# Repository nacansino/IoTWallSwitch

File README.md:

# IoTWallSwitch
An open-source IoT Wall Switch based on ESP device. I based this project on Xoseperez's [espurna-board project](https://github.com/xoseperez/espurna-board).

I aim this project to be a foundation of many small projects that ran on tap power supply.

## Block Diagram

## Primary Functionalities (User perspective):
1. Act as an on/off switch of an alternating or direct current load; the method of switching shall be done via physical access (e.g. button, capacitive touch) or via wirelessly (web interface, telnet, etc.)
2. Has the capability to measure the power consumed by the load, and to report it to an external entity (cloud, local household server).
3. Support more than one wireless protocol for redundancy
4. Has the capability to update functionality after deployment without physical access (over-the-air or OTA updates).

## Tech Stack
- Schematic and Layout: KiCAD
- Toolchain: TBA, currently thinking of building over ESP-IDF
- Unit Testing: CppUTest

## Applications:
- Generic Smart Switch for any load below 10A
- Household and industrial lighting
- Small motors/fans/pumps
- Desktop/Laptop Charger
- Television
- Speakers

## 3D Preview

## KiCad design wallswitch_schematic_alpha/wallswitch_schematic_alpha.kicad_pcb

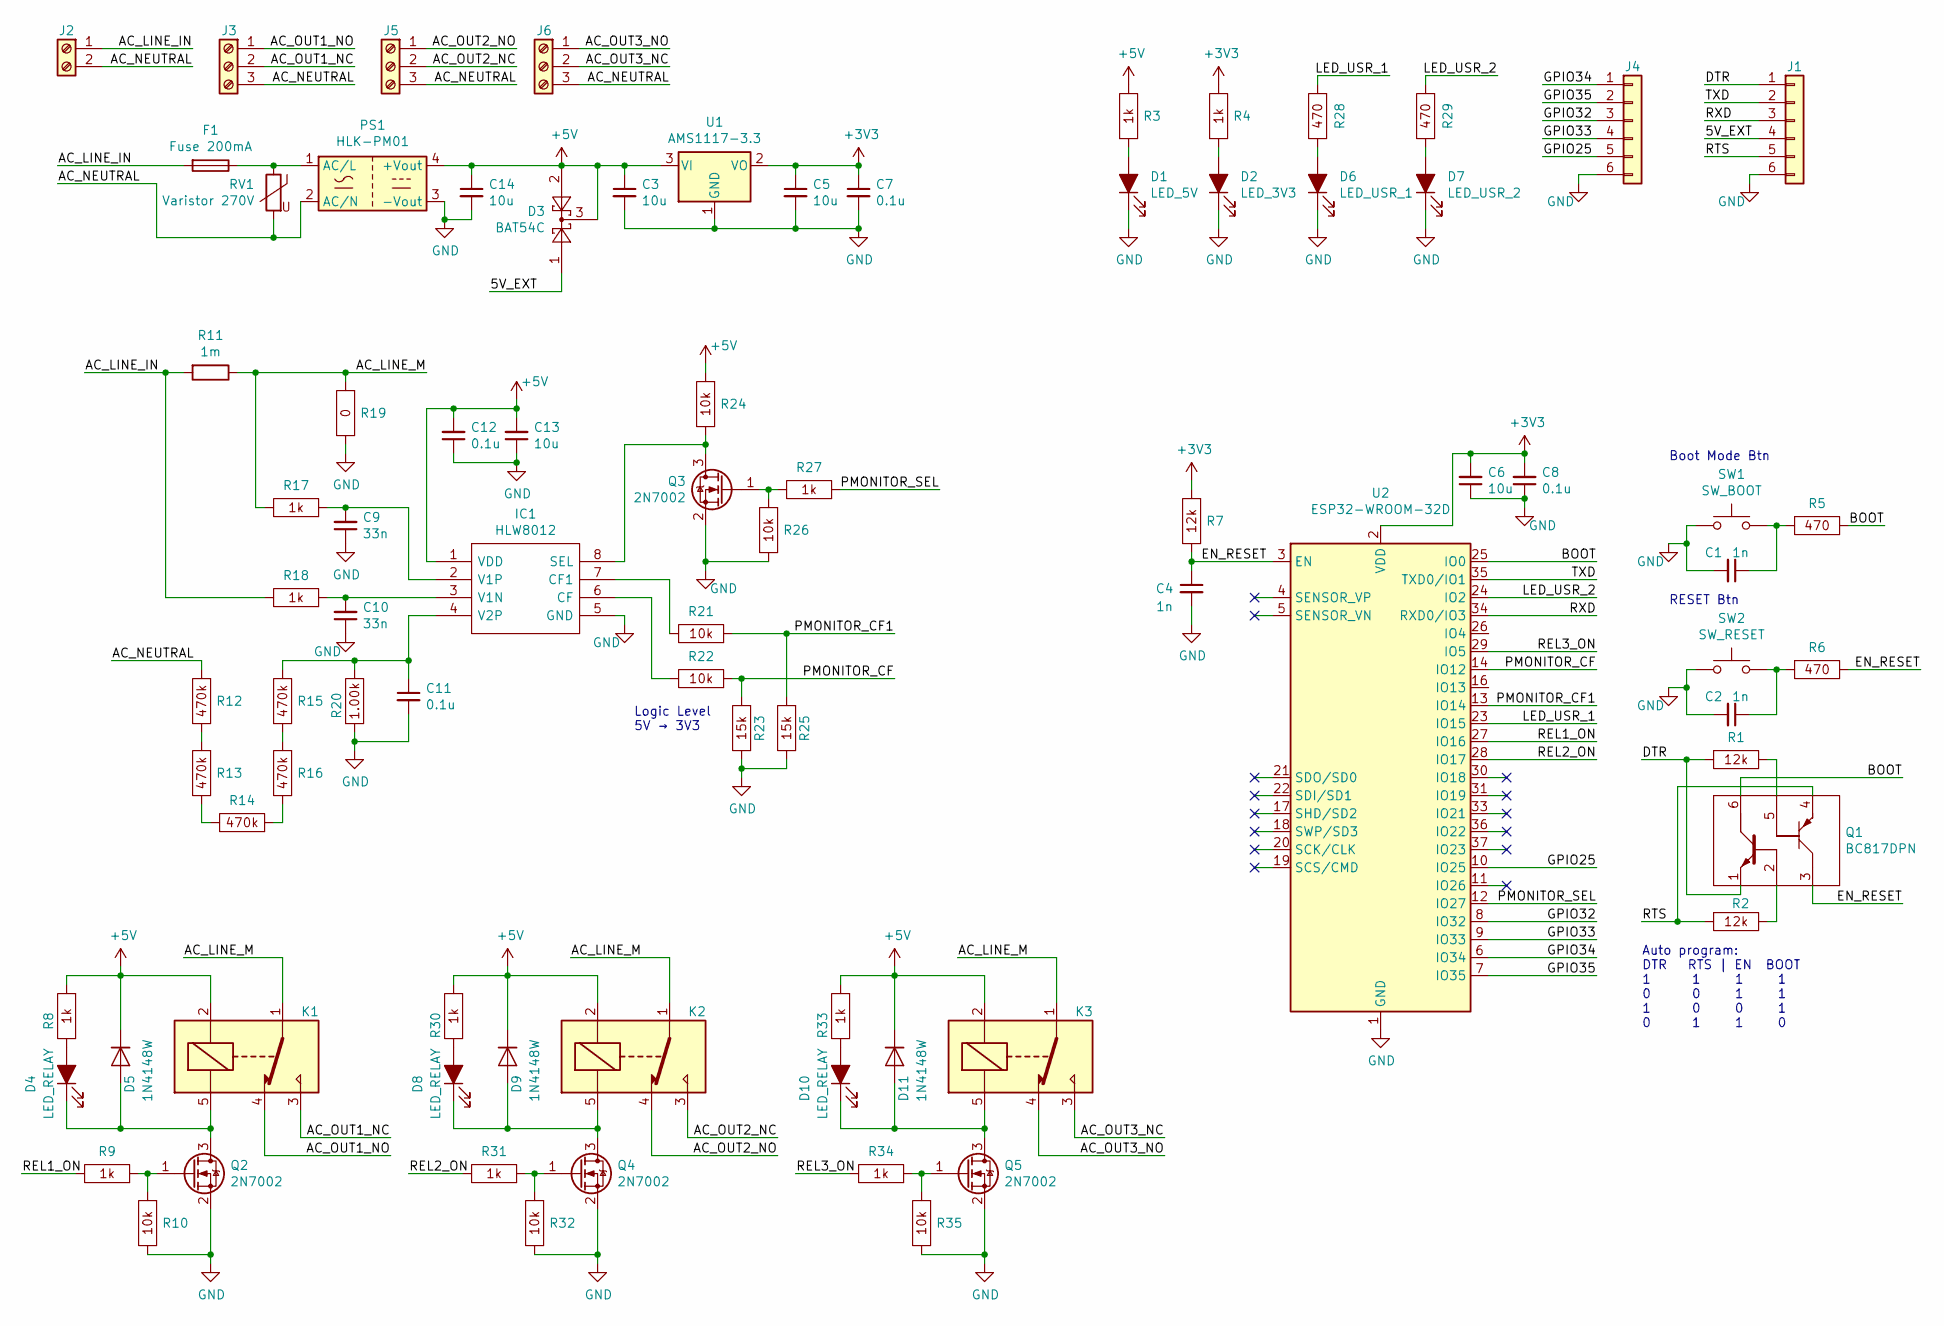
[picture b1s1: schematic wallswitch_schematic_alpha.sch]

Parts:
C1, C2, C4: 1n; C_0603_1608Metric
C3, C5, C6, C13, C14: 10u; C_0603_1608Metric
C7, C8, C11, C12: 0.1u; C_0603_1608Metric
C9, C10: 33n; C_0603_1608Metric
D1: LED_5V; LED_0603_1608Metric
D2: LED_3V3; LED_0603_1608Metric
D3: BAT54C; SOT-23
D4, D8, D10: LED_RELAY; LED_0603_1608Metric
D5, D9, D11: 1N4148W; D_SOD-123
D6: LED_USR_1; LED_0603_1608Metric
D7: LED_USR_2; LED_0603_1608Metric
F1: Fuse 200mA; Fuse_Blade_Mini_directSolder
IC1: HLW8012; SOIC127P600X170-8N; Manufacturer_Part_Number HLW8012
J1, J4: Conn_01x06; PinHeader_1x06_P2.54mm_Vertical
J2: Screw_Terminal_01x02; TerminalBlock_bornier-2_P5.08mm
J3, J5, J6: Screw_Terminal_01x03; TerminalBlock_bornier-3_P5.08mm
K1, K2, K3: SANYOU_SRD_Form_C; Relay_SPDT_SANYOU_SRD_Series_Form_C
PS1: HLK-PM01; Converter_ACDC_HiLink_HLK-PMxx
Q1: BC817DPN; SOT95P275X110-6N; Manufacturer_Part_Number BC817DPN; Mouser Part Number N/A
Q2, Q3, Q4, Q5: 2N7002; SOT-23
R1, R2, R7: R_12k_±5%_1608m; R_0603_1608Metric; Power Rating 0.1W; Tolerance ±5%
R3, R4, R8, R9, R17, R18, R27, R30, R31, R33, R34: R_1k_±5%_1608m; R_0603_1608Metric; Power Rating 0.125W; Tolerance ±5%
R5, R6, R28, R29: R_470_±5%_1608m; R_0603_1608Metric; Power Rating 0.125W; Tolerance ±5%
R10, R21, R22, R24, R26, R32, R35: R_10k_±5%_1608m; R_0603_1608Metric; Power Rating 0.1W; Tolerance ±5%
R11: 1m; R_2512_6332Metric_Pad1.52x3.35mm_HandSolder
R12, R13, R14, R15, R16: R_470k_±1%_1608m; R_0603_1608Metric; Power Rating 0.1W; Tolerance ±1%
R19: R_0_―_1608m; R_0603_1608Metric; Power Rating 1A; Tolerance ―
R20: R_1.00k_±1%_1608m; R_0603_1608Metric; Power Rating 0.125W; Tolerance ±1%
R23, R25: R_15k_±5%_1608m; R_0603_1608Metric; Power Rating 0.1W; Tolerance ±5%
RV1: Varistor 270V; RV_Disc_D12mm_W3.9mm_P7.5mm
SW1: SW_BOOT; SW_SPST_CK_RS282G05A3
SW2: SW_RESET; SW_SPST_CK_RS282G05A3
U1: AMS1117-3.3; SOT-223-3_TabPin2
U2: ESP32-WROOM-32D; ESP32-WROOM-32

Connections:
+3V3: C5.1, C6.2, C7.1, C8.2, R4.2, R7.1, U1.2 (VO), U2.2 (VDD)
+5V: C3.1, C12.2, C13.2, C14.1, D3.2, D3.3, D5.1 (K), D9.1 (K), D11.1 (K), IC1.1 (VDD), K1.2, K2.2, K3.2, PS1.4 (+Vout), R3.2, R8.1, R24.1, R30.1, R33.1, U1.3 (VI)
/5V_EXT: D3.1, J1.4
/AC_LINE_IN: F1.2, J2.1, R11.2, R18.2
/AC_LINE_M: K1.1, K2.1, K3.1, R11.1, R17.2, R19.1
/AC_NEUTRAL: J2.2, J3.3, J5.3, J6.3, PS1.2 (AC/N), R12.1, RV1.2
/AC_OUT1_NC: J3.2, K1.3
/AC_OUT1_NO: J3.1, K1.4
/AC_OUT2_NC: J5.2, K2.3
/AC_OUT2_NO: J5.1, K2.4
/AC_OUT3_NC: J6.2, K3.3
/AC_OUT3_NO: J6.1, K3.4
/BOOT: Q1.6, R5.2, U2.25 (IO0)
/DTR: J1.1, Q1.1, R1.1
/EN_RESET: C4.1, Q1.3, R6.2, R7.2, U2.3 (EN)
/GPIO25: J4.5, U2.10 (IO25)
/GPIO32: J4.3, U2.8 (IO32)
/GPIO33: J4.4, U2.9 (IO33)
/GPIO34: J4.1, U2.6 (IO34)
/GPIO35: J4.2, U2.7 (IO35)
/LED_USR_1: R28.1, U2.23 (IO15)
/LED_USR_2: R29.1, U2.24 (IO2)
/PMONITOR_CF: R22.1, R23.1, U2.14 (IO12)
/PMONITOR_CF1: R21.1, R25.1, U2.13 (IO14)
/PMONITOR_SEL: R27.1, U2.12 (IO27)
/REL1_ON: R9.2, U2.27 (IO16)
/REL2_ON: R31.2, U2.28 (IO17)
/REL3_ON: R34.2, U2.29 (IO5)
/RTS: J1.5, Q1.4, R2.1
/RXD: J1.3, U2.34 (RXD0/IO3)
/TXD: J1.2, U2.35 (TXD0/IO1)
GND: C1.2, C2.2, C3.2, C4.2, C5.2, C6.1, C7.2, C8.1, C9.1, C10.1, C11.2, C12.1, C13.1, C14.2, D1.1 (K), D2.1 (K), D6.1 (K), D7.1 (K), IC1.5 (GND), J1.6, J4.6, PS1.3 (-Vout), Q2.2 (S), Q3.2 (S), Q4.2 (S), Q5.2 (S), R10.2, R19.2, R20.1, R23.2, R25.2, R26.2, R32.2, R35.2, SW1.1, SW2.1, U1.1 (GND), U2.1 (GND), U2.15 (GND), U2.38 (GND), U2.39 (GND)
unnamed: C1.1, R5.1, SW1.2
unnamed: C2.1, R6.1, SW2.2
unnamed: C9.2, IC1.2 (V1P), R17.1
unnamed: C10.2, IC1.3 (V1N), R18.1
unnamed: C11.1, IC1.4 (V2P), R15.2, R20.2
unnamed: D1.2 (A), R3.1
unnamed: D2.2 (A), R4.1
unnamed: D4.1 (K), D5.2 (A), K1.5, Q2.3 (D)
unnamed: D4.2 (A), R8.2
unnamed: D6.2 (A), R28.2
unnamed: D7.2 (A), R29.2
unnamed: D8.1 (K), D9.2 (A), K2.5, Q4.3 (D)
unnamed: D8.2 (A), R30.2
unnamed: D10.1 (K), D11.2 (A), K3.5, Q5.3 (D)
unnamed: D10.2 (A), R33.2
unnamed: F1.1, PS1.1 (AC/L), RV1.1
unnamed: IC1.6 (CF), R22.2
unnamed: IC1.7 (CF1), R21.2
unnamed: IC1.8 (SEL), Q3.3 (D), R24.2
unnamed: Q1.2, R2.2
unnamed: Q1.5, R1.2
unnamed: Q2.1 (G), R9.1, R10.1
unnamed: Q3.1 (G), R26.1, R27.2
unnamed: Q4.1 (G), R31.1, R32.1
unnamed: Q5.1 (G), R34.1, R35.1
unnamed: R12.2, R13.1
unnamed: R13.2, R14.2
unnamed: R14.1, R16.2
unnamed: R15.1, R16.1

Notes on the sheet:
Logic Level 5V → 3V3
Auto program: DTR RTS | EN BOOT 1 1 1 1 0 0 1 1 1 0 0 1 0 1 1 0
Boot Mode Btn
RESET Btn

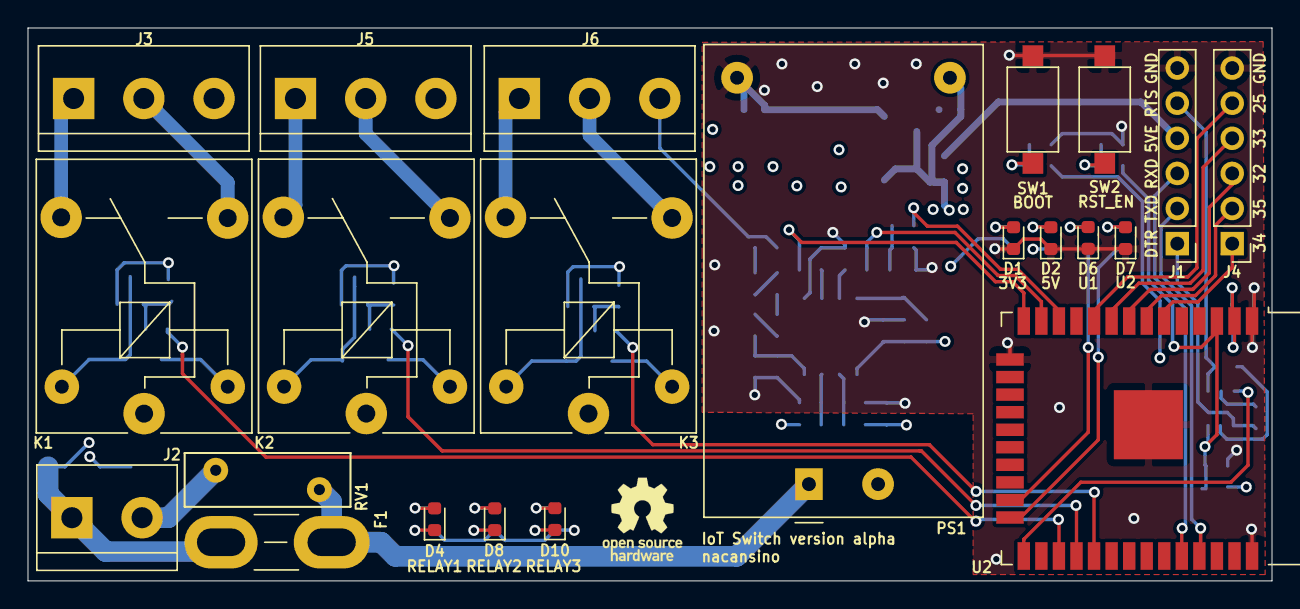
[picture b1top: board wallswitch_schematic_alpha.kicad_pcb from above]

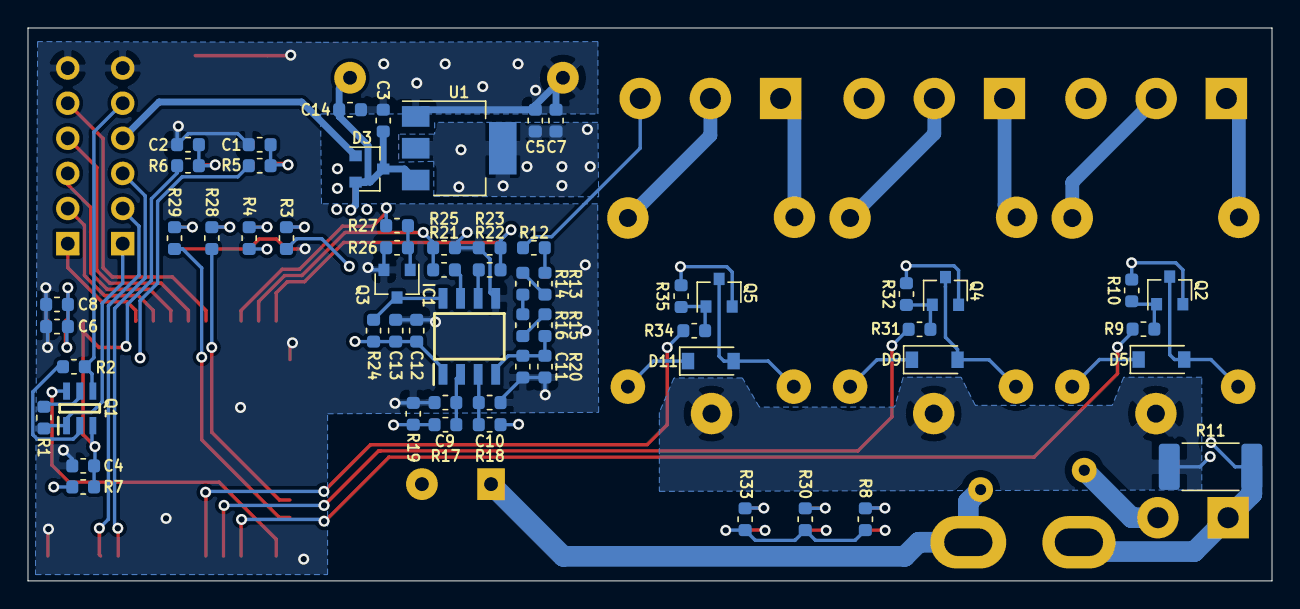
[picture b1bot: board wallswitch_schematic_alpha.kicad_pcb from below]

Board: 4 copper layers, 90.0 x 40.0 mm, 82 parts (60 on the bottom side), 61 nets.

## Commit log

2020-05-24 added block diagram
2020-05-24 added circuit
2020-05-24 added wall switch
2020-05-24 updated block diagram resolution
2020-05-24 schematic - added components
2020-05-24 added peripheral circuit (50%)
2020-05-31 added esp32 general datasheet
2020-05-31 updated peripheral circuits
2020-06-13 added components
2020-06-21 added v0.0 library
2020-06-28 added XLAB libraries onboard
2020-06-28 removed SamacSys_Parts dependency
2020-06-28 removed samacsys lib
2020-06-28 Revert "removed samacsys lib"
    This reverts commit f6d89dbcb364026727547d694c52e7e328d72772.
2020-06-28 added XLAB_Block to symbol and library path#
2020-06-28 added *.kicad_pcb-bak to ignore list
2020-06-28 added XLAB_Block
2020-06-28 modification of some components to use new XLAB footprint
2020-06-28 ignored bak file
2020-06-28 1. Attached appropriate footprint to connectors 2. TODO: Capacitors and varistor
2020-07-19 progress for layout
2020-10-11 finished artwork
2020-10-11 added 3d picture to readme
2020-10-24 modification to generate gerber files
